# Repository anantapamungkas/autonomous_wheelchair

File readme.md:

## 📁 Struktur Repositori

Rrepositori terdiri dari beberapa komponen utama:
*   **`assets/`**: 
*   **`firmware/`**: 
*   **`hardware/`**: 
*   **`ros_ws/`**: 
*   **`scripts/`**: 

## Spesifikasi Perangkat Keras (Hardware)

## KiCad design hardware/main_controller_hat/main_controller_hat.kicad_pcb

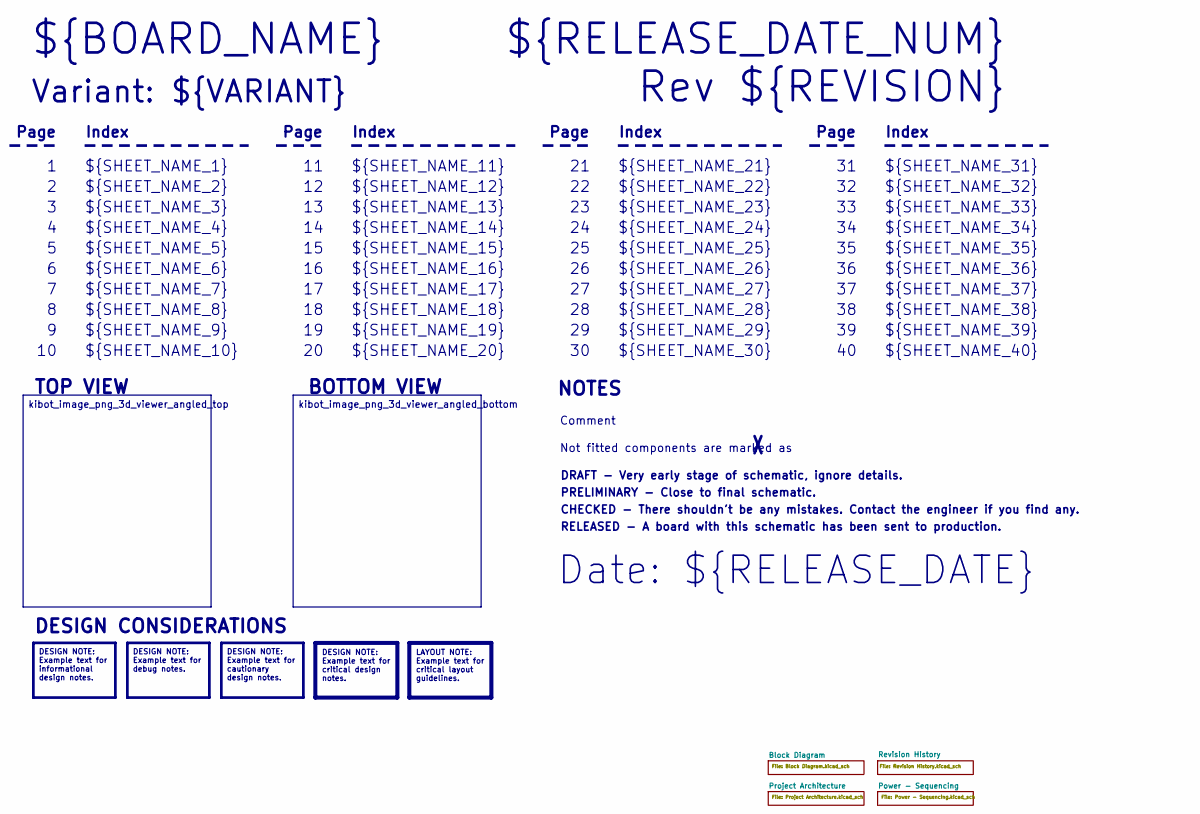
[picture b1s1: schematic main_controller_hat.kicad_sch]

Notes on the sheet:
Variant: ${VARIANT}
RELEASED - A board with this schematic has been sent to production.
${SHEET_NAME_24}
Index
Page
PRELIMINARY - Close to final schematic.
${SHEET_NAME_22}
DRAFT - Very early stage of schematic, ignore details.
${SHEET_NAME_12}
${SHEET_NAME_8}
${SHEET_NAME_2}
${SHEET_NAME_5}
${SHEET_NAME_20}
${SHEET_NAME_23}
${RELEASE_DATE_NUM}
${SHEET_NAME_35}
Not fitted components are marked as
${SHEET_NAME_11}
${SHEET_NAME_6}
${SHEET_NAME_37}
${SHEET_NAME_26}
${SHEET_NAME_36}
Rev ${REVISION}
${SHEET_NAME_15}
CHECKED - There shouldn't be any mistakes. Contact the engineer if you find any.
BOTTOM VIEW
${SHEET_NAME_14}
${SHEET_NAME_21}
${SHEET_NAME_17}
${SHEET_NAME_18}
Date: ${RELEASE_DATE}
${SHEET_NAME_7}
${SHEET_NAME_31}
${BOARD_NAME}
NOTES
${SHEET_NAME_40}
${SHEET_NAME_39}
${SHEET_NAME_32}
${SHEET_NAME_1}
${SHEET_NAME_9}

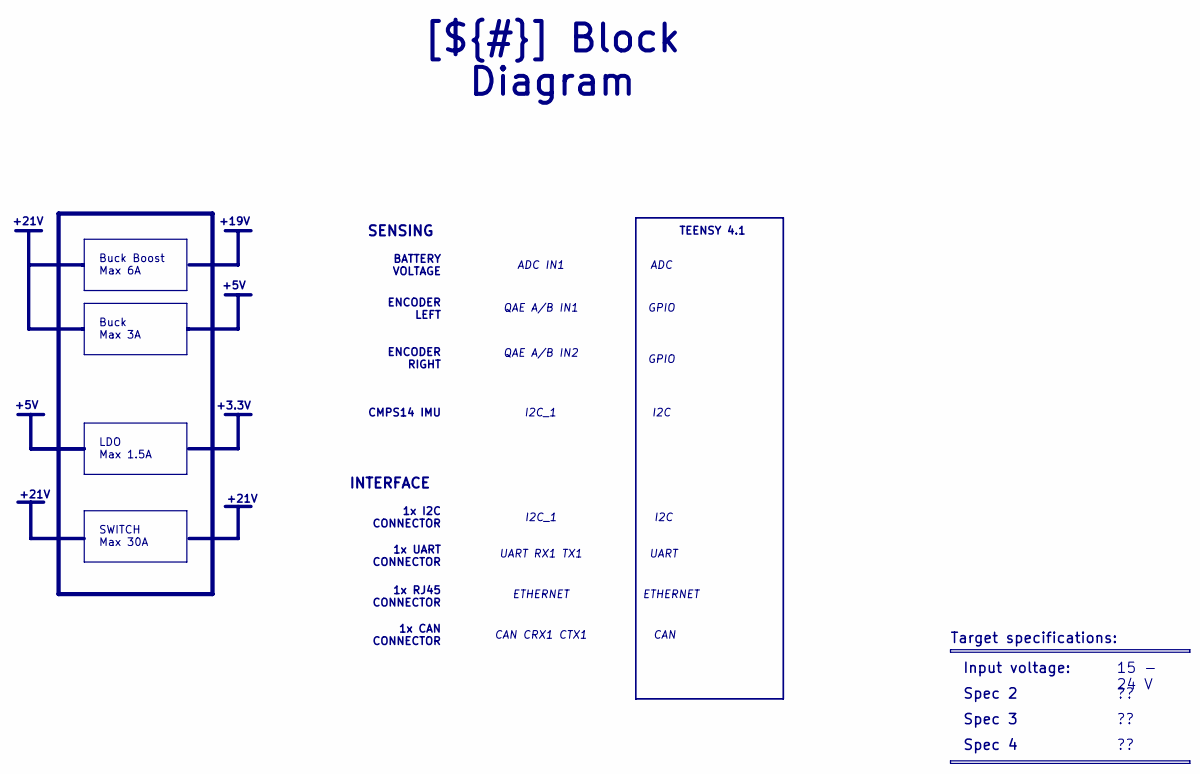
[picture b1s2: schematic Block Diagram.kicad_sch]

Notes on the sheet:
+21V
+5V
TEENSY 4.1
+3.3V
+19V
CMPS14 IMU
Spec 4
15 - 24 V
ENCODER LEFT ENCODER RIGHT
1x CAN CONNECTOR
ETHERNET
ADC
Buck Boost Max 6A
1x UART CONNECTOR
LDO Max 1.5A
CAN CRX1 CTX1
QAE A/B IN1
UART
GPIO
I2C
[${#}] ${TITLE}
QAE A/B IN2
Input voltage:
SENSING
1x RJ45 CONNECTOR
Target specifications:
1x I2C CONNECTOR
Spec 3
Spec 2
I2C_1
Buck Max 3A
BATTERY VOLTAGE
ADC IN1
SWITCH Max 30A
UART RX1 TX1
CAN
INTERFACE

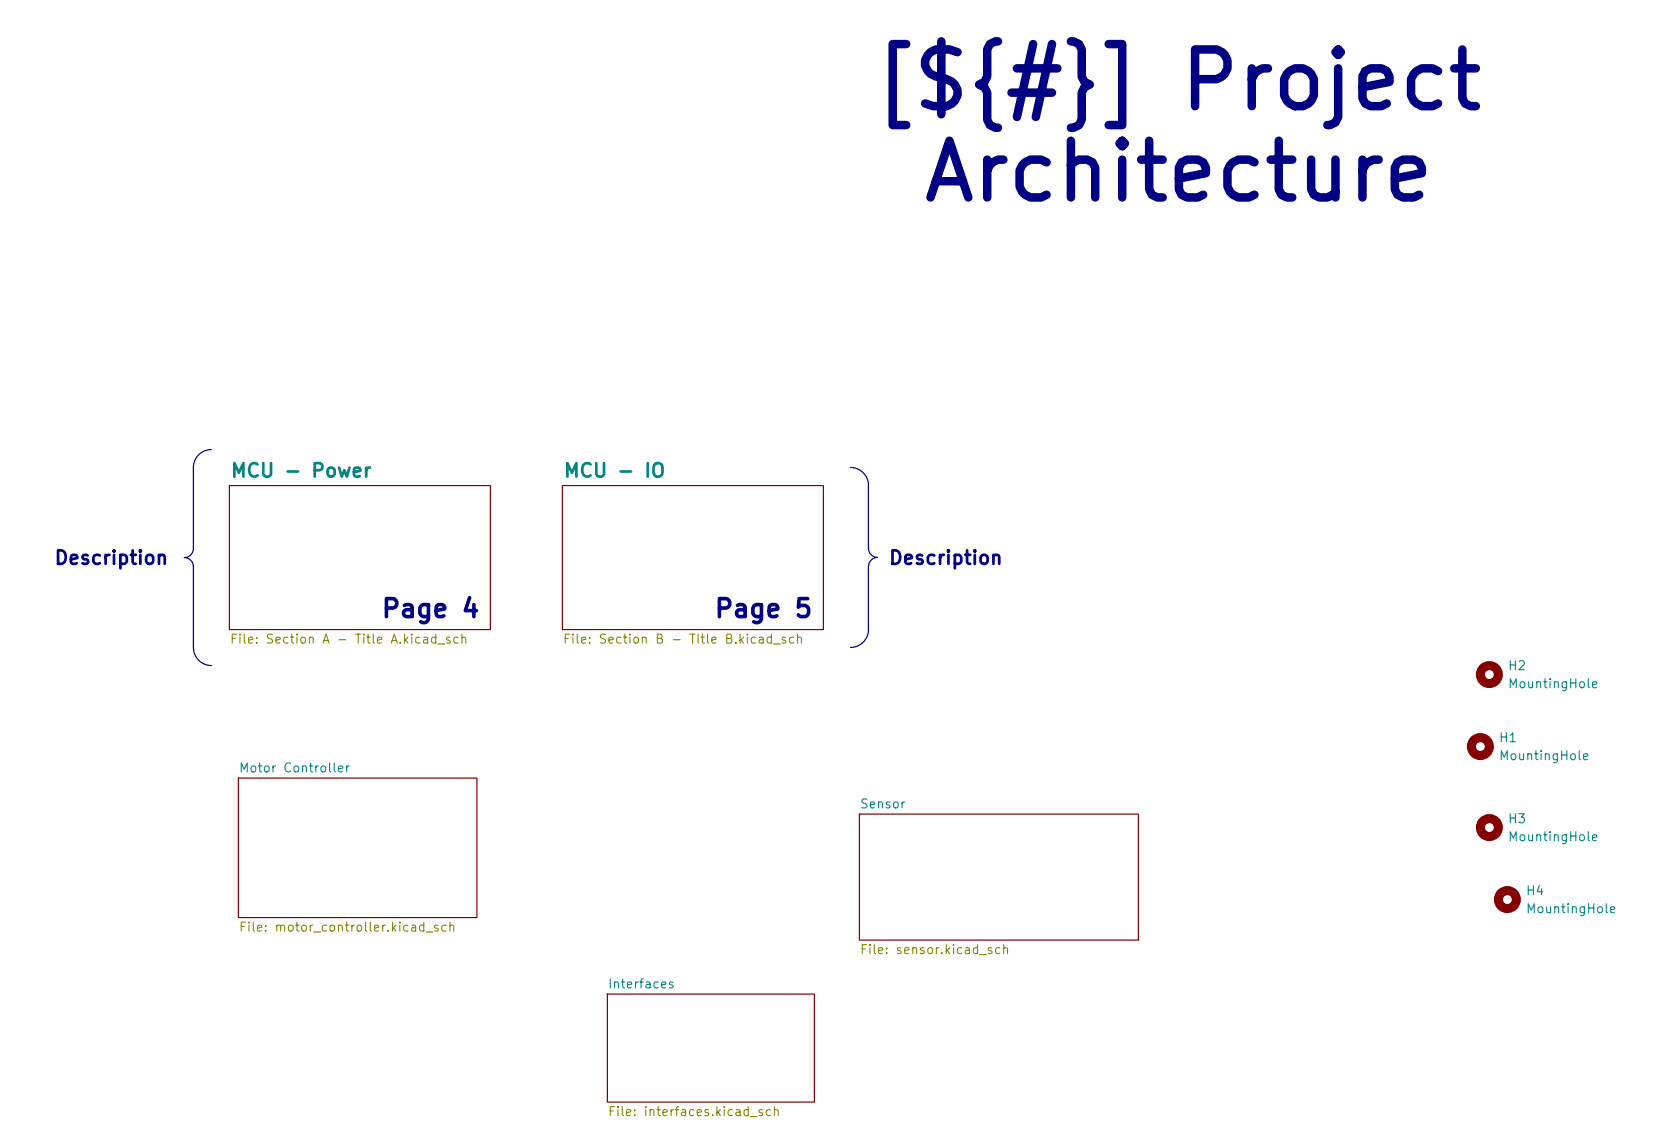
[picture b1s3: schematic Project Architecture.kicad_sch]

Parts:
H1, H2, H3, H4: MountingHole; MountingHole_3.2mm_M3_DIN965_Pad_TopBottom

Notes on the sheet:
Page 5
Page 4
Description
[${#}] ${TITLE}

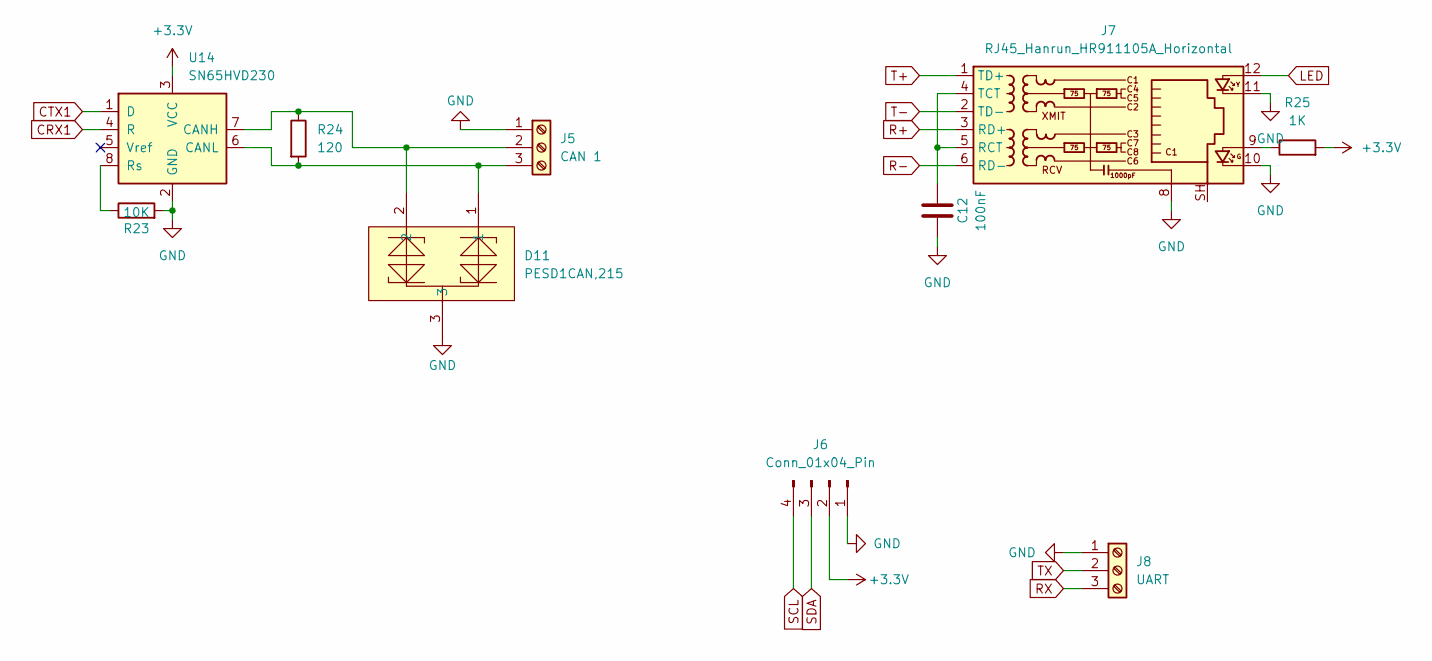
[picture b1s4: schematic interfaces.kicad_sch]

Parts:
C12: 100nF; C_0805_2012Metric
D11: PESD1CAN,215; SOT-23_L2.9-W1.3-P1.90-LS2.4-BR; MPN PESD1CAN,215; LCSC Part C15771
J5: CAN 1; PhoenixContact_MSTBA_2,5_3-G-5,08_1x03_P5.08mm_Horizontal
J6: Conn_01x04_Pin; JST_XH_B4B-XH-A_1x04_P2.50mm_Vertical
J7: RJ45_Hanrun_HR911105A_Horizontal
J8: UART; PhoenixContact_MSTBA_2,5_3-G-5,08_1x03_P5.08mm_Horizontal
R23: 10K; R_0805_2012Metric
R24: 120; R_0805_2012Metric
R25: 1K; R_0805_2012Metric
U14: SN65HVD230; SOIC-8_3.9x4.9mm_P1.27mm

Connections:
+3.3V: J6.2, R25.2, U14.3 (VCC); also elsewhere on the board
CRX1: U14.4 (R); also elsewhere on the board
CTX1: U14.1 (D); also elsewhere on the board
GND: C12.1, D11.3, J5.1, J6.1, J7.8, J7.10, J7.11, J8.1, R23.2, U14.2 (GND); also elsewhere on the board
LED: J7.12; also elsewhere on the board
unnamed: D11.2, J5.2, R24.1, U14.7 (CANH)
unnamed: D11.1, J5.3, R24.2, U14.6 (CANL)
unnamed: J7.9, R25.1
unnamed: C12.2, J7.4 (TCT), J7.5 (RCT)
unnamed: R23.1, U14.8 (Rs)
R+: J7.3 (RD+); also elsewhere on the board
R-: J7.6 (RD-); also elsewhere on the board
RX: J8.3; also elsewhere on the board
SCL: J6.4; also elsewhere on the board
SDA: J6.3; also elsewhere on the board
T+: J7.1 (TD+); also elsewhere on the board
T-: J7.2 (TD-); also elsewhere on the board
TX: J8.2; also elsewhere on the board

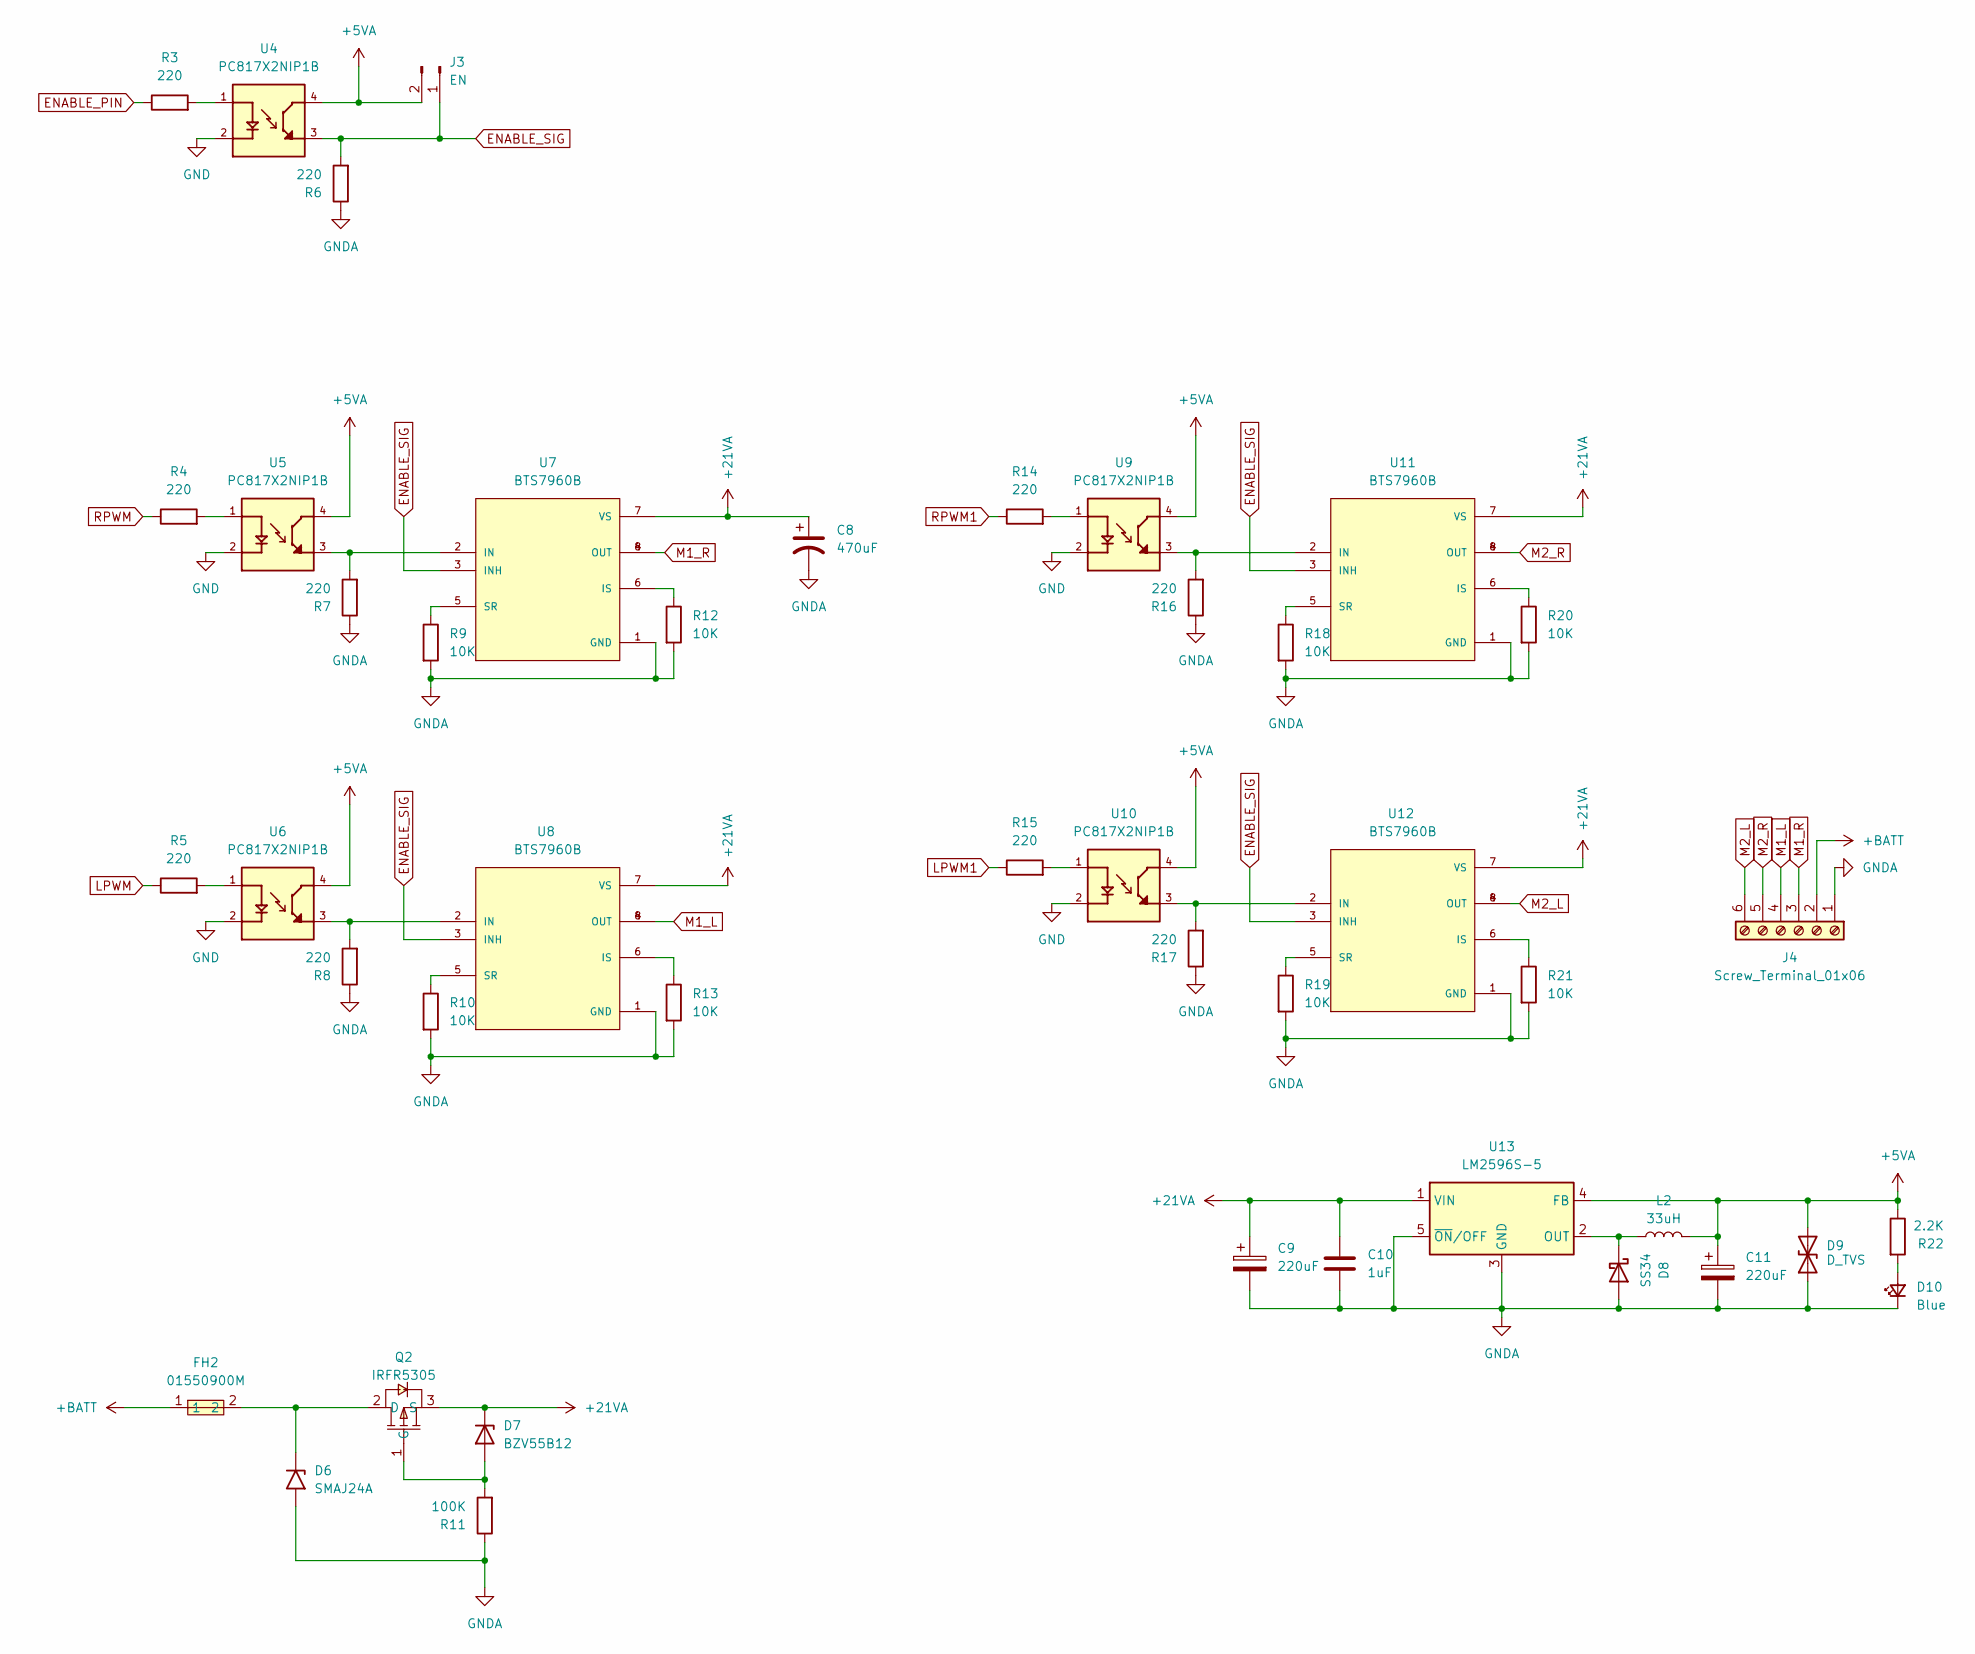
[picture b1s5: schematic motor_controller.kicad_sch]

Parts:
C8: 470uF; CP_Elec_10x10; Voltage 50V
C9, C11: 220uF; CP_Elec_8x10.5
C10: 1uF; C_0805_2012Metric
D6: SMAJ24A; D_SMA
D7: BZV55B12; D_MiniMELF
D8: SS34; SMA_L4.4-W2.8-LS5.4-R-RD
D9: D_TVS; D_SMA
D10: Blue; LED_0805_2012Metric
FH2: 01550900M; FUSE-SMD_L9.8-W5.0_01550900M; MPN 01550900M; LCSC Part C108518
J3: EN; PinSocket_1x02_P2.54mm_Vertical
J4: Screw_Terminal_01x06; TerminalBlock_Phoenix_MKDS-1,5-6-5.08_1x06_P5.08mm_Horizont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
L2: 33uH; INDM7676X435N
Q2: IRFR5305; TO-252-3_L6.6-W6.1-P4.58-LS10.1-BR-1; MPN IRFR5305; LCSC Part C5155388
R3, R4, R5, R6, R7, R8, R14, R15, R16, R17: 220; R_0805_2012Metric
R9, R10, R12, R13, R18, R19, R20, R21: 10K; R_0805_2012Metric
R11: 100K; R_0805_2012Metric
R22: 2.2K; R_0805_2012Metric
U4, U5, U6, U9, U10: PC817X2NIP1B; SOIC254P960X420-4N; PARTREV October 12, 2016
U7, U8, U11, U12: BTS7960B; DPAK127P1490X440-8N; PARTREV 1.1
U13: LM2596S-5; TO-263-5_TabPin3

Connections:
+5VA: C11.1, D9.2 (A2), J3.2, L2.2, R22.1, U4.4, U5.4, U6.4, U9.4, U10.4, U13.4 (FB)
+21VA: C8.1, C9.1, C10.1, D7.1 (K), Q2.3 (S), U7.7 (VS), U8.7 (VS), U11.7 (VS), U12.7 (VS), U13.1 (VIN)
+BATT: FH2.1, J4.2
ENABLE_PIN: R3.1; also elsewhere on the board
ENABLE_SIG: J3.1, R6.2, U4.3, U7.3 (INH), U8.3 (INH), U11.3 (INH), U12.3 (INH)
GND: U4.2, U5.2, U6.2, U9.2, U10.2; also elsewhere on the board
GNDA: C8.2, C9.2, C10.2, C11.2, D6.2 (A2), D8.2 (A), D9.1 (A1), D10.1 (K), J4.1, R6.1, R7.1, R8.1, R9.2, R10.2, R11.1, R12.2, R13.2, R16.1, R17.1, R18.2, R19.2, R20.2, R21.2, U7.1 (GND), U8.1 (GND), U11.1 (GND), U12.1 (GND), U13.3 (GND), U13.5 (~ON/OFF)
LPWM: R5.1; also elsewhere on the board
LPWM1: R15.1; also elsewhere on the board
M1_L: J4.4, U8.4 (OUT), U8.8 (OUT)
M1_R: J4.3, U7.4 (OUT), U7.8 (OUT)
M2_L: J4.6, U12.4 (OUT), U12.8 (OUT)
M2_R: J4.5, U11.4 (OUT), U11.8 (OUT)
unnamed: D6.1 (A1), FH2.2, Q2.2 (D)
unnamed: D7.2 (A), Q2.1 (G), R11.2
unnamed: D8.1 (K), L2.1, U13.2 (OUT)
unnamed: D10.2 (A), R22.2
unnamed: R3.2, U4.1
unnamed: R4.2, U5.1
unnamed: R5.2, U6.1
unnamed: R14.2, U9.1
unnamed: R15.2, U10.1
unnamed: R7.2, U5.3, U7.2 (IN)
unnamed: R12.1, U7.6 (IS)
unnamed: R9.1, U7.5 (SR)
unnamed: R8.2, U6.3, U8.2 (IN)
unnamed: R13.1, U8.6 (IS)
unnamed: R10.1, U8.5 (SR)
unnamed: R16.2, U9.3, U11.2 (IN)
unnamed: R20.1, U11.6 (IS)
unnamed: R18.1, U11.5 (SR)
unnamed: R17.2, U10.3, U12.2 (IN)
unnamed: R21.1, U12.6 (IS)
unnamed: R19.1, U12.5 (SR)
RPWM: R4.1; also elsewhere on the board
RPWM1: R14.1; also elsewhere on the board

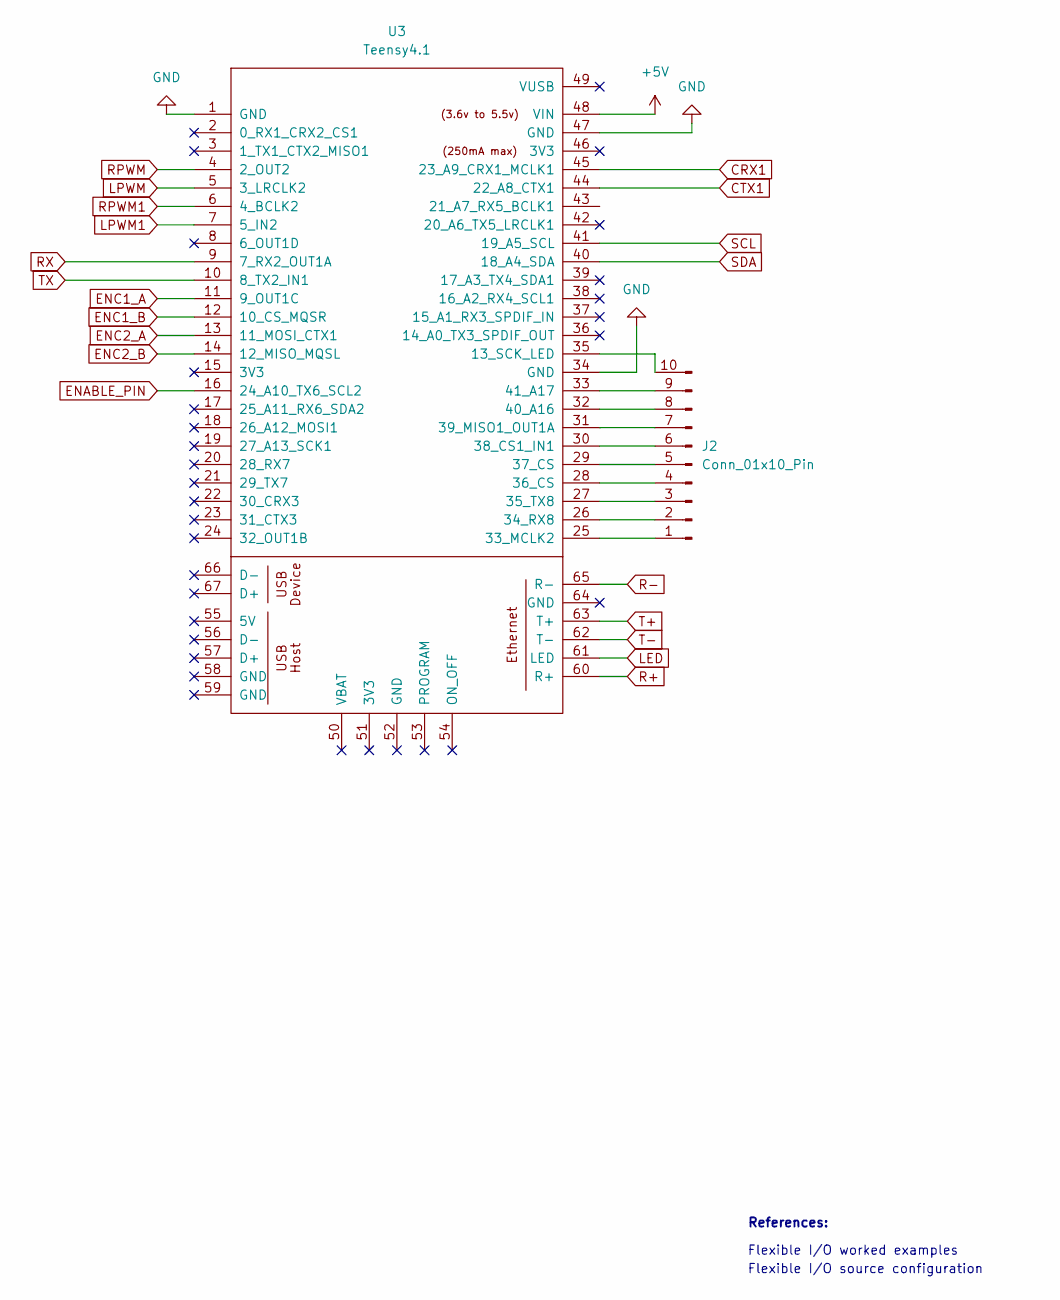
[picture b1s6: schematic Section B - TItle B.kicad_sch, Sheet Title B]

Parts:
J2: Conn_01x10_Pin; PinHeader_1x10_P2.54mm_Vertical
U3: Teensy4.1; Teensy41

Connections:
+5V: U3.48 (VIN); also elsewhere on the board
CRX1: U3.45 (23_A9_CRX1_MCLK1); also elsewhere on the board
CTX1: U3.44 (22_A8_CTX1); also elsewhere on the board
ENABLE_PIN: U3.16 (24_A10_TX6_SCL2); also elsewhere on the board
ENC1_A: U3.11 (9_OUT1C); also elsewhere on the board
ENC1_B: U3.12 (10_CS_MQSR); also elsewhere on the board
ENC2_A: U3.13 (11_MOSI_CTX1); also elsewhere on the board
ENC2_B: U3.14 (12_MISO_MQSL); also elsewhere on the board
GND: U3.1 (GND), U3.34 (GND), U3.47 (GND); also elsewhere on the board
LED: U3.61 (LED); also elsewhere on the board
LPWM: U3.5 (3_LRCLK2); also elsewhere on the board
LPWM1: U3.7 (5_IN2); also elsewhere on the board
unnamed: J2.1, U3.25 (33_MCLK2)
unnamed: J2.2, U3.26 (34_RX8)
unnamed: J2.3, U3.27 (35_TX8)
unnamed: J2.4, U3.28 (36_CS)
unnamed: J2.5, U3.29 (37_CS)
unnamed: J2.6, U3.30 (38_CS1_IN1)
unnamed: J2.7, U3.31 (39_MISO1_OUT1A)
unnamed: J2.8, U3.32 (40_A16)
unnamed: J2.9, U3.33 (41_A17)
unnamed: J2.10, U3.35 (13_SCK_LED)
R+: U3.60 (R+); also elsewhere on the board
R-: U3.65 (R-); also elsewhere on the board
RPWM: U3.4 (2_OUT2); also elsewhere on the board
RPWM1: U3.6 (4_BCLK2); also elsewhere on the board
RX: U3.9 (7_RX2_OUT1A); also elsewhere on the board
SCL: U3.41 (19_A5_SCL); also elsewhere on the board
SDA: U3.40 (18_A4_SDA); also elsewhere on the board
T+: U3.63 (T+); also elsewhere on the board
T-: U3.62 (T-); also elsewhere on the board
TX: U3.10 (8_TX2_IN1); also elsewhere on the board

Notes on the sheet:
Flexible I/O worked examples
References:
Flexible I/O source configuration

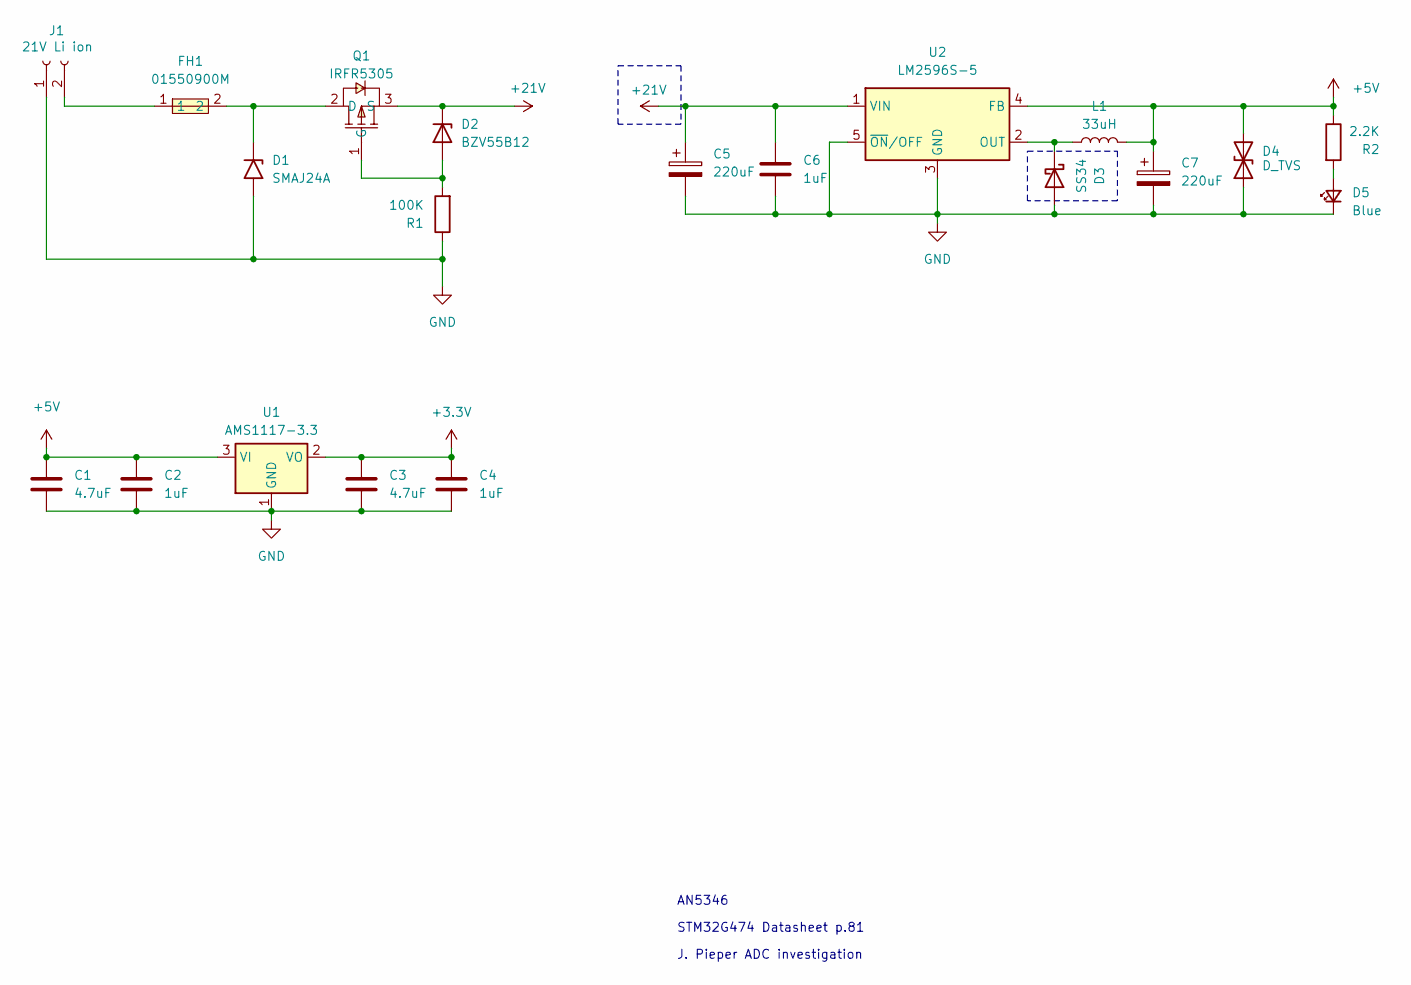
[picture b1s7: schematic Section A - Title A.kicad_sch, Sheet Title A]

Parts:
C1, C3: 4.7uF; C_1206_3216Metric
C2, C4, C6: 1uF; C_0805_2012Metric
C5, C7: 220uF; CP_Elec_8x10.5
D1: SMAJ24A; D_SMA
D2: BZV55B12; D_MiniMELF
D3: SS34; SMA_L4.4-W2.8-LS5.4-R-RD
D4: D_TVS; D_SMA
D5: Blue; LED_0805_2012Metric
FH1: 01550900M; FUSE-SMD_L9.8-W5.0_01550900M; MPN 01550900M; LCSC Part C108518
J1: 21V Li ion; TerminalBlock_Phoenix_MKDS-3-2-5.08_1x02_P5.08mm_Horizontal
L1: 33uH; INDM7676X435N
Q1: IRFR5305; TO-252-3_L6.6-W6.1-P4.58-LS10.1-BR-1; MPN IRFR5305; LCSC Part C5155388
R1: 100K; R_0805_2012Metric
R2: 2.2K; R_0805_2012Metric
U1: AMS1117-3.3; SOT-223-3_TabPin2
U2: LM2596S-5; TO-263-5_TabPin3

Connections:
+3.3V: C3.1, C4.1, U1.2 (VO); also elsewhere on the board
+5V: C1.1, C2.1, C7.1, D4.2 (A2), L1.2, R2.1, U1.3 (VI), U2.4 (FB); also elsewhere on the board
+21V: C5.1, C6.1, D2.1 (K), Q1.3 (S), U2.1 (VIN)
GND: C1.2, C2.2, C3.2, C4.2, C5.2, C6.2, C7.2, D1.2 (A2), D3.2 (A), D4.1 (A1), D5.1 (K), J1.1, R1.1, U1.1 (GND), U2.3 (GND), U2.5 (~ON/OFF); also elsewhere on the board
unnamed: D1.1 (A1), FH1.2, Q1.2 (D)
unnamed: D2.2 (A), Q1.1 (G), R1.2
unnamed: D3.1 (K), L1.1, U2.2 (OUT)
unnamed: D5.2 (A), R2.2
unnamed: FH1.1, J1.2

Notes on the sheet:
J. Pieper ADC investigation
STM32G474 Datasheet p.81
AN5346

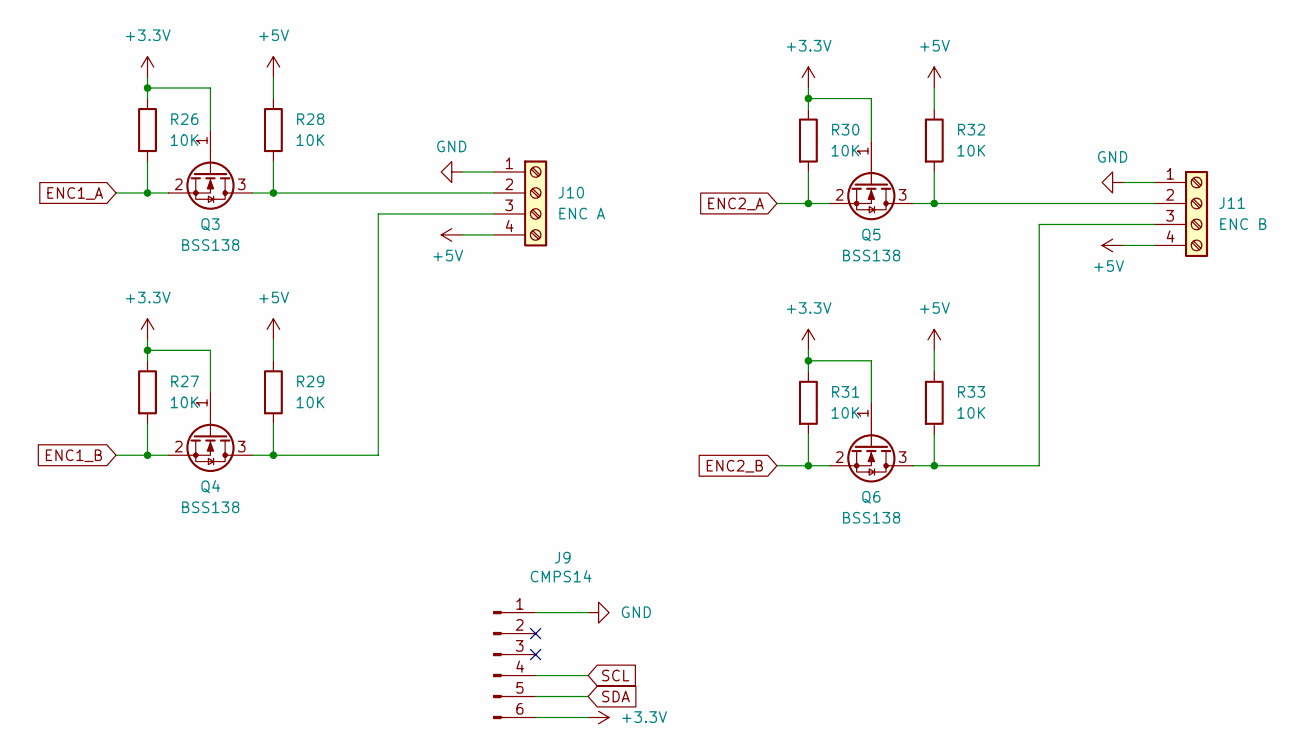
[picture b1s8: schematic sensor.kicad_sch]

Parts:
J9: CMPS14; PinHeader_1x06_P2.54mm_Vertical
J10: ENC A; PhoenixContact_MSTBA_2,5_4-G-5,08_1x04_P5.08mm_Horizontal
J11: ENC B; PhoenixContact_MSTBA_2,5_4-G-5,08_1x04_P5.08mm_Horizontal
Q3, Q4, Q5, Q6: BSS138; SOT-23
R26, R27, R28, R29, R30, R31, R32, R33: 10K; R_0805_2012Metric

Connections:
+3.3V: J9.6, Q3.1 (G), Q4.1 (G), Q5.1 (G), Q6.1 (G), R26.1, R27.1, R30.1, R31.1; also elsewhere on the board
+5V: J10.4, J11.4, R28.1, R29.1, R32.1, R33.1; also elsewhere on the board
ENC1_A: Q3.2 (S), R26.2; also elsewhere on the board
ENC1_B: Q4.2 (S), R27.2; also elsewhere on the board
ENC2_A: Q5.2 (S), R30.2; also elsewhere on the board
ENC2_B: Q6.2 (S), R31.2; also elsewhere on the board
GND: J9.1, J10.1, J11.1; also elsewhere on the board
unnamed: J10.2, Q3.3 (D), R28.2
unnamed: J10.3, Q4.3 (D), R29.2
unnamed: J11.2, Q5.3 (D), R32.2
unnamed: J11.3, Q6.3 (D), R33.2
SCL: J9.4; also elsewhere on the board
SDA: J9.5; also elsewhere on the board

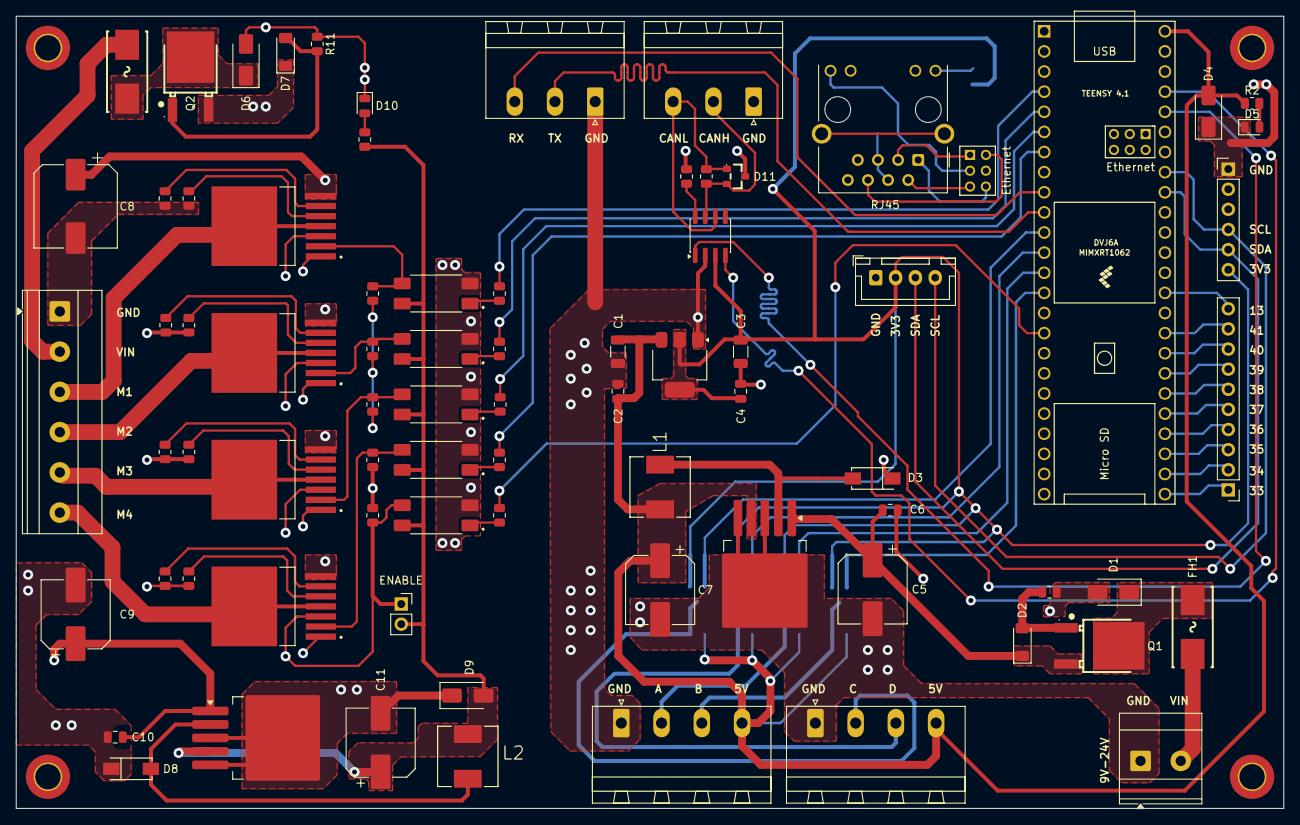
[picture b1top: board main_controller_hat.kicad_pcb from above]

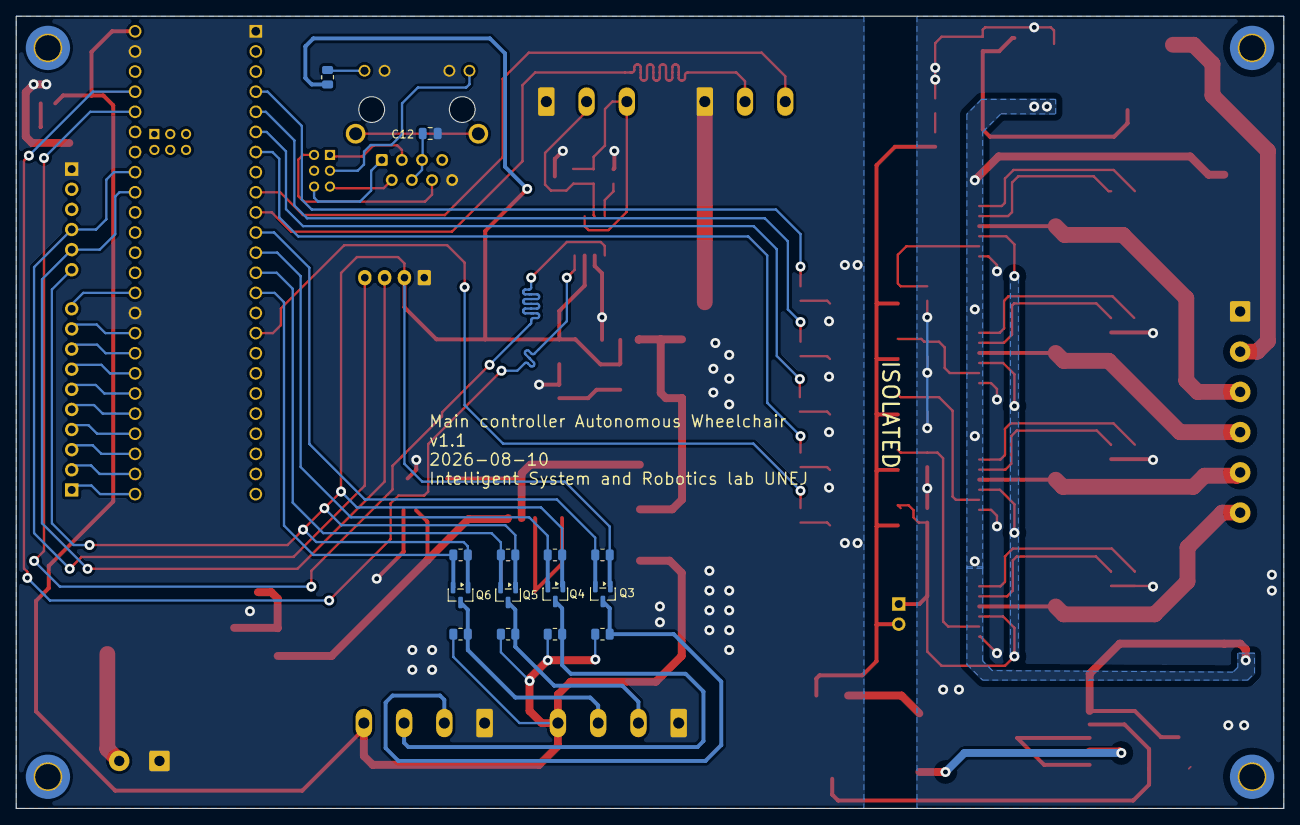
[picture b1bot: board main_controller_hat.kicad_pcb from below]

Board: 6 copper layers, 160.0 x 100.0 mm, 95 parts (14 on the bottom side), 78 nets.

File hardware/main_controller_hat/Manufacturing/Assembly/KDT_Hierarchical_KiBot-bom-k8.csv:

"#","Qty","Reference","Value","Datasheet","Footprint","Description","Manufacturer","Manufacturer Part Number"
"1","83","C1,C2,C3,C4,C5,C6,C7,C8,C10,C11,C12,C13,D1,D2,D3,D4,D5,D6,D7,D8,D9,D10,D11,FH1,FH2,J1,J2,J3,J4,J5,J6,J7,J8,J9,J14,L1,L2,Q1,Q2,Q3,Q4,Q5,Q6,R1,R2,R3,R4,R5,R6,R7,R8,R9,R10,R11,R12,R13,R14,R15,R16,R17,R18,R19,R20,R21,R22,R23,R24,R25,R26,R27,U1,U3,U5,U6,U7,U8,U9,U10,U11,U12,U13,U14,U15","01550900M,100K,100nF,10K,120,1K,1uF,2.2K,21V Li ion,220uF,33uH,4.7uF,470uF,6N137,AMS1117-3.3,BSS138,BTS7960B,BZV55B12,Blue,CAN 1,CMPS14,Conn_01x04_Pin,Conn_01x10_Pin,D_TVS,ENC A,ENC B,IRFR5305,LM2596S-5,PESD1CAN,215,RJ45_Hanrun_HR911105A_Horizontal,SMAJ24A,SN65HVD230,SS34,Screw_Terminal_01x06,Teensy4.1,UART","http://www.advanced-monolithic.com/pdf/ds1117.pdf,http://www.ti.com/lit/ds/symlink/lm2596.pdf,http://www.ti.com/lit/ds/symlink/sn65hvd230.pdf,https://assets.nexperia.com/documents/data-sheet/BZV55_SER.pdf,https://datasheet.lcsc.com/lcsc/1811141815_HANRUN-Zhongshan-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,https://docs.broadcom.com/docs/AV02-0940EN,https://lcsc.com/product-detail/Diodes-ESD_NXP_PESD1CAN_PESD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,https://lcsc.com/product-detail/Others_Littelfuse_01550900M_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,https://media.digikey.com/pdf/Data%20Sheets/Rohm%20PDFs/SMLE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,https://www.lcsc.com/datasheet/C5155388.pdf,https://www.lcsc.com/product-detail/C72480.html,https://www.littelfuse.com/media?resourcetype=datasheets&ite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,https://www.onsemi.com/pub/Collateral/BSS138-D.PDF","BTS7960B:DPAK127P1490X440-8N,Capacitor_SMD:CP_Elec_10x10,Capacitor_SMD:CP_Elec_8x10.5,Capacitor_SMD:C_0603_1608Metric,Capacitor_SMD:C_0603_1608Metric_Pad1.08x0.95mm_HandSolder,Capacitor_SMD:C_1206_3216Metric_Pad1.33x1.80mm_HandSolder,Connector_JST:JST_XH_B4B-XH-A_1x04_P2.50mm_Vertical,Connector_Phoenix_MSTB:PhoenixContact_MSTBA_2,5_3-G-5,08_1x03_P5.08mm_Horizontal,Connector_Phoenix_MSTB:PhoenixContact_MSTBA_2,5_4-G-5,08_1x04_P5.08mm_Horizontal,Connector_PinHeader_2.54mm:PinHeader_1x06_P2.54mm_Vertical,Connector_PinHeader_2.54mm:PinHeader_1x10_P2.54mm_Vertical,Connector_RJ:RJ45_Hanrun_HR911105A_Horizontal,DR74-330-R:INDM7676X435N,Diode_SMD:D_MiniMELF,Diode_SMD:D_SMA,PCM_SparkFun-LED:LED_0805_2012Metric,PCM_SparkFun-Resistor:R_0805_2012Metric,Package_DIP:DIP-8_W7.62mm,Package_SO:SOIC-8_3.9x4.9mm_P1.27mm,Package_TO_SOT_SMD:SOT-223-3_TabPin2,Package_TO_SOT_SMD:SOT-23,Package_TO_SOT_SMD:TO-263-5_TabPin3,Resistor_SMD:R_0603_1608Metric_Pad0.98x0.95mm_HandSolder,TerminalBlock_Phoenix:TerminalBlock_Phoenix_MKDS-1,5-6-5.08_1x06_P5.08mm_Horizontal,TerminalBlock_Phoenix:TerminalBlock_Phoenix_MKDS-3-2-5.08_1x02_P5.08mm_Horizontal,easyeda2kicad:FUSE-SMD_L9.8-W5.0_01550900M,easyeda2kicad:SMA_L4.4-W2.8-LS5.4-R-RD,easyeda2kicad:SOT-23_L2.9-W1.3-P1.90-LS2.4-BR,easyeda2kicad:TO-252-3_L6.6-W6.1-P4.58-LS10.1-BR-1,teensy:Teensy41","1 Port RJ45 Magjack Connector Through Hole 10/100 Base-T, AutoMDIX,12V, 500mW, 2%, Zener diode, MiniMELF,1A Low Dropout regulator, positive, 3.3V fixed output, SOT-223,400W unidirectional Transient Voltage Suppressor, 24.0Vr, SMA(DO-214AC),50V Vds, 0.22A Id, N-Channel MOSFET, SOT-23,5V 3A Step-Down Voltage Regulator, TO-263,Bidirectional transient-voltage-suppression diode,CAN Bus Transceivers, 3.3V, 1Mbps, Low-Power capabilities, SOIC-8,Generic connector, single row, 01x02, script generated,Generic connector, single row, 01x04, script generated,Generic connector, single row, 01x06, script generated,Generic connector, single row, 01x10, script generated,Generic screw terminal, single row, 01x03, script generated (kicad-library-utils/schlib/autogen/connector/),Generic screw terminal, single row, 01x04, script generated (kicad-library-utils/schlib/autogen/connector/),Generic screw terminal, single row, 01x06, script generated (kicad-library-utils/schlib/autogen/connector/),Inductor,Light emitting diode,PESD1CAN,Polarized capacitor,Polarized capacitor, US symbol,Resistor,Schottky diode,Single High Speed LSTTL/TTL Compatible Optocoupler with enable, dV/dt 1000/us, VCM 10, max 7V VCC, DIP-8,Unpolarized capacitor","Littelfuse(美国力特),Nexperia(安世),Slkor(萨科微)",""
